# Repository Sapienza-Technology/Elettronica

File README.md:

# Elettronica rover Technology Team

## Utili

- [Git repo](https://github.com/Sapienza-Technology-2021/Elettronica)
- [Homepage European Rover Challenge](https://roverchallenge.eu/en/main-page/)
- [Regolamento Challenge](https://drive.google.com/file/d/1fdFG12WW0QmHjRp6cL2ikP8UFmEpzSka/view)

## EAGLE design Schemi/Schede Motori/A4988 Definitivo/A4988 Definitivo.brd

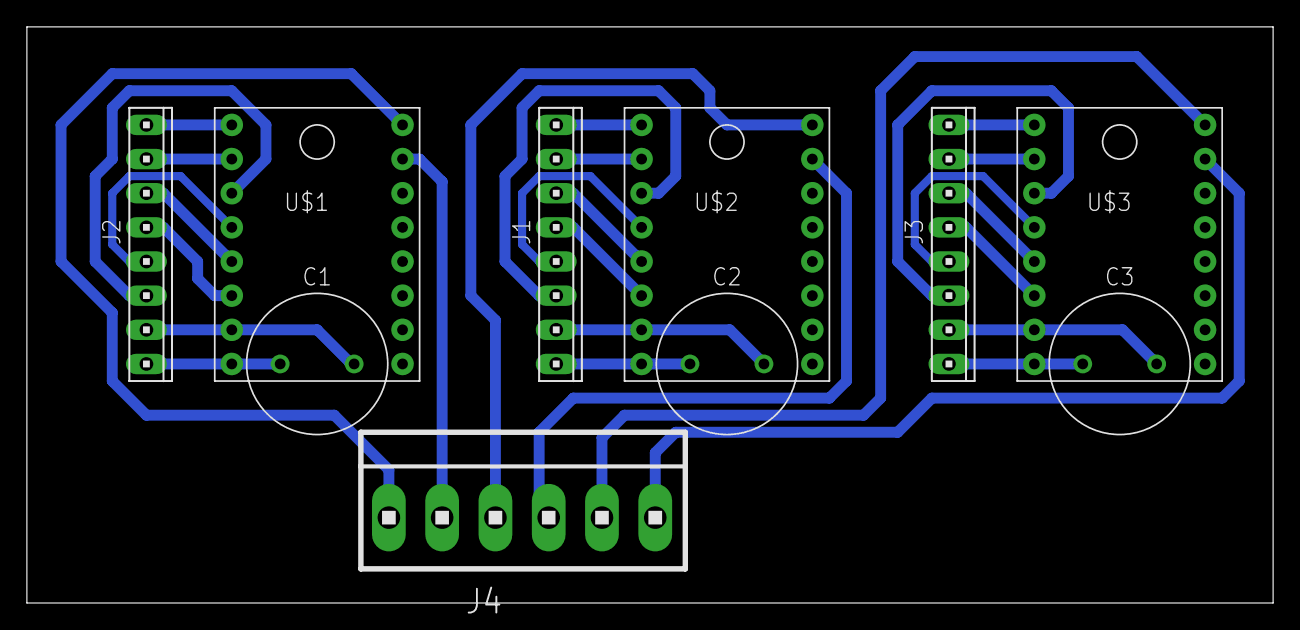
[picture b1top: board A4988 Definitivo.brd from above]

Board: 2 copper layers, 92.7 x 42.8 mm, 10 parts (0 on the bottom side), 30 nets.

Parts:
C1, C2, C3: CAPRD550W60D1025H1250B
J1, J2, J3: 10X08MTA
J4: 1X6MTA
U$1, U$2, U$3: BOARD_A4988

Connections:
unnamed: C2.1, J1.1, U$2.VMOT
unnamed: C2.2, J1.2, U$2.GNDMOT
unnamed: J1.3, U$2.M1B
unnamed: J1.4, U$2.M1A
unnamed: J1.5, U$2.M2AB
unnamed: J1.6, U$2.M2A
unnamed: J1.7, U$2.+5V
unnamed: J1.8, U$2.GND
unnamed: C3.1, J3.1, U$3.VMOT
unnamed: C1.1, J2.1, U$1.VMOT
unnamed: C1.2, J2.2, U$1.GNDMOT
unnamed: C3.2, J3.2, U$3.GNDMOT
unnamed: J2.3, U$1.M1B
unnamed: J2.4, U$1.M1A
unnamed: J2.5, U$1.M2AB
unnamed: J2.6, U$1.M2A
unnamed: J2.7, U$1.+5V
unnamed: J2.8, U$1.GND
unnamed: J3.3, U$3.M1B
unnamed: J3.4, U$3.M1A
unnamed: J3.5, U$3.M2AB
unnamed: J3.6, U$3.M2A
unnamed: J3.7, U$3.+5V
unnamed: J3.8, U$3.GND
unnamed: J4.6, U$1.DIR
unnamed: J4.5, U$1.STEP
unnamed: J4.4, U$2.DIR
unnamed: J4.3, U$2.STEP
unnamed: J4.2, U$3.DIR
unnamed: J4.1, U$3.STEP

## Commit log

2021-03-06 Prova Cadlab
2021-03-06 Cancella prova
2021-03-06 Prova prova
2021-03-06 Caricamento File
2021-03-06 LISTA COMPONENTI ELETTRONICI
2021-03-23 Riorganizzazione
2022-06-11 Schemi
2022-07-30 Upload firmware
2022-08-28 firmware braccio
2022-08-30 firmware braccio update
2022-09-02 arduino
2022-09-02 Aggiunto tutti i motori, ora si possono muovere
2022-09-27 Firmware usato durante la competizione
2022-09-27 Mega commit di firmware ruote
2022-12-10 Created multiple main files to test different techniques
2022-12-24 modified wheel firmware
2023-07-13 firmware per movimento CC8
2023-07-13 un po' di fix, ora builda con successo
2023-07-25 stepper test and multi main
2023-08-27 added firmware for structure and arm
2023-09-02 added a joint
2023-09-09 Gripper addition and reductions change
2023-09-10 new firmware for structure
2023-09-11 Overflow avoidance
2023-09-11 drillling firmware
2023-09-12 drilling firmware for arduino
2023-09-12 removed a not used pin
2023-09-12 to check later
2023-09-14 new pinmap structure
2023-09-14 new firmware for arm esp
2023-09-14 change to
2023-09-14 Correction in gripper firmware
2024-01-14 Fix and integration of encoders in Esp firmware Addition of simple Arduino Uno test code
2024-01-16 Fix to ESP firmware with encoders
2024-02-02 Fix stepper velocity control and ROS integration
2024-02-09 Add joint initialization values to MyStepper constructor
2024-02-15 Fix main-firmware for firmware_braccio_esp package
2024-02-17 Fix encoder init
2024-03-12 Aggiunti file firmware in posizione (senza encoder)
    Sistemato script main firmware esp (con encoder)
    - in firmware esp commentata riga per comandare la velocità ricevuta da nodo ros
2024-03-23 Fix libreria ros per esp32 Fix firmware esp in posizione eliminando dipendenza da AccelStepperI2C
